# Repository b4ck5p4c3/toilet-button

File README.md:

# toilet-button

B4CKSP4CE button panel in toilet

Written for WCH MCU CH32V003J4M6

## Building

Install WCH [toolchain](https://xpack.github.io/dev-tools/riscv-none-elf-gcc/) to `~/wch/xpack-riscv-none-elf-gcc-12.2.0-1/bin` or change path in `cmake/toolchain-ch32v00x.cmake` file

Run `cmake . && cmake --build .`

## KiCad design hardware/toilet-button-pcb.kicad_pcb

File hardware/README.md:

# hardware

Hardware part of button panel in toilet

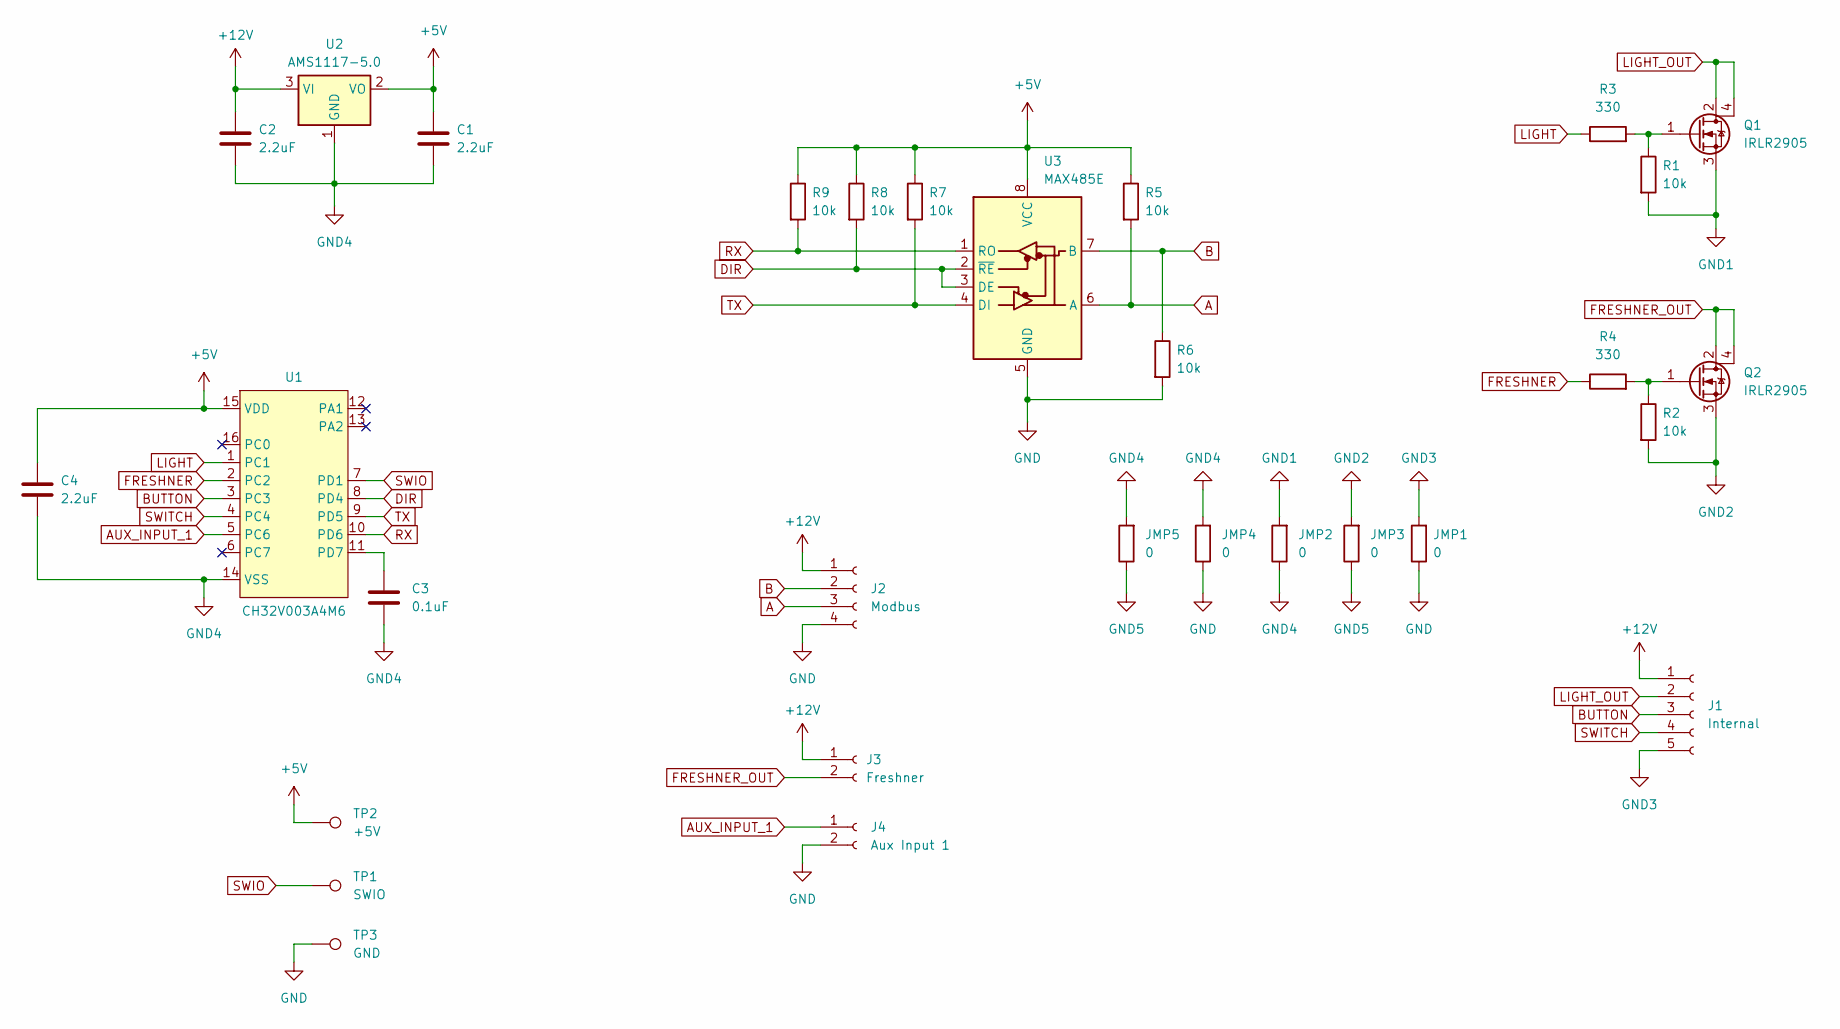
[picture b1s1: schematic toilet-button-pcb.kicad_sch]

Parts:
C1, C2, C4: 2.2uF; C_1206_3216Metric
C3: 0.1uF; C_1206_3216Metric
J1: Internal; JST_XH_5_SMD
J2: Modbus; Terminal_4_SMD
J3: Freshner; Terminal_2_SMD
J4: Aux Input 1; Terminal_2_SMD
JMP1, JMP2, JMP3, JMP4, JMP5: 0; R_1206_3216Metric
Q1, Q2: IRLR2905; TO-252-3_TabPin4
R1, R2, R5, R6, R7, R8, R9: 10k; R_1206_3216Metric
R3, R4: 330; R_1206_3216Metric
TP1: SWIO; TestPoint_Pad_D2.0mm
TP2: +5V; TestPoint_Pad_D2.0mm
TP3: GND; TestPoint_Pad_D2.0mm
U1: CH32V003A4M6; SOP-16_3.9x9.9mm_P1.27mm
U2: AMS1117-5.0; SOT-223-3_TabPin2
U3: MAX485E; SO-8_3.9x4.9mm_P1.27mm

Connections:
+5V: C1.1, C4.1, R5.1, R7.1, R8.1, R9.1, TP2.1, U1.15 (VDD), U2.2 (VO), U3.8 (VCC)
+12V: C2.1, J1.1, J2.1, J3.1, U2.3 (VI)
A: J2.3, R5.2, U3.6 (A)
AUX_INPUT_1: J4.1, U1.5 (PC6)
B: J2.2, R6.1, U3.7 (B)
BUTTON: J1.3, U1.3 (PC3)
DIR: R8.2, U1.8 (PD4), U3.2 (~RE), U3.3 (DE)
FRESHNER: R4.1, U1.2 (PC2)
FRESHNER_OUT: J3.2, Q2.2 (D), Q2.4 (D)
GND: J2.4, J4.2, JMP1.1, JMP4.1, R6.2, TP3.1, U3.5 (GND)
GND1: JMP2.2, Q1.3 (S), R1.2
GND2: JMP3.2, Q2.3 (S), R2.2
GND3: J1.5, JMP1.2
GND4: C1.2, C2.2, C3.2, C4.2, JMP2.1, JMP4.2, JMP5.2, U1.14 (VSS), U2.1 (GND)
GND5: JMP3.1, JMP5.1
LIGHT: R3.1, U1.1 (PC1)
LIGHT_OUT: J1.2, Q1.2 (D), Q1.4 (D)
unnamed: Q1.1 (G), R1.1, R3.2
unnamed: Q2.1 (G), R2.1, R4.2
unnamed: C3.1, U1.11 (PD7)
RX: R9.2, U1.10 (PD6), U3.1 (RO)
SWIO: TP1.1, U1.7 (PD1)
SWITCH: J1.4, U1.4 (PC4)
TX: R7.2, U1.9 (PD5), U3.4 (DI)

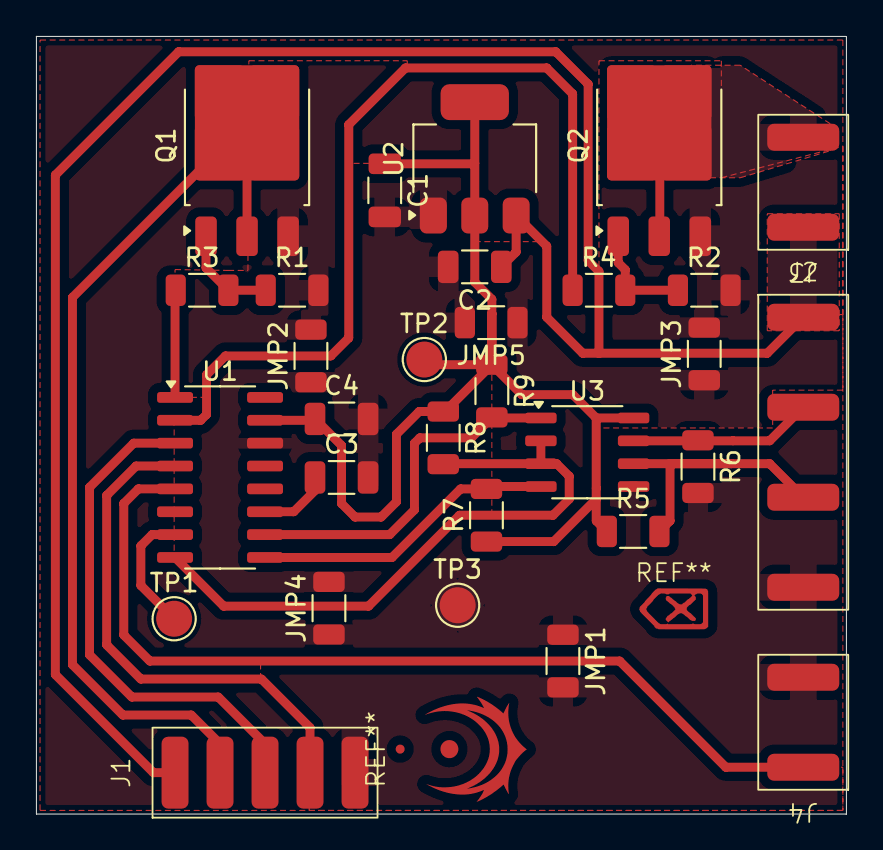
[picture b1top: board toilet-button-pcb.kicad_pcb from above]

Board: 2 copper layers, 45.0 x 43.2 mm, 30 parts (0 on the bottom side), 24 nets.

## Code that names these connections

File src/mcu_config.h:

#ifndef TOILET_BUTTON_MCU_CONFIG_H
#define TOILET_BUTTON_MCU_CONFIG_H

#include <ch32v00x.h>

#define MODBUS_UART USART1
#define MODBUS_SPEED 115200
#define MODBUS_SLAVE_ID 228

#define TX_PORT GPIOD
#define TX_PIN GPIO_Pin_5

#define RX_PORT GPIOD
#define RX_PIN GPIO_Pin_6

#define DIR_PORT GPIOD
#define DIR_PIN GPIO_Pin_4

#define LIGHT_PORT GPIOC
#define LIGHT_PIN GPIO_Pin_1

#define FRESHNER_PORT GPIOC
#define FRESHNER_PIN GPIO_Pin_2

#define BUTTON_PORT GPIOC
#define BUTTON_PIN GPIO_Pin_3
#define BUTTON_PORT_SOURCE GPIO_PortSourceGPIOC
#define BUTTON_PIN_SOURCE GPIO_PinSource3
#define BUTTON_EXTI_LINE EXTI_Line3

#define SWITCH_PORT GPIOC
#define SWITCH_PIN GPIO_Pin_4

#define AUX_INPUT_1_PORT GPIOC
#define AUX_INPUT_1_PIN GPIO_Pin_6

#endif  //TOILET_BUTTON_MCU_CONFIG_H

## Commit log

2024-10-27 main commit
2025-11-13 Add MIT License to the project
